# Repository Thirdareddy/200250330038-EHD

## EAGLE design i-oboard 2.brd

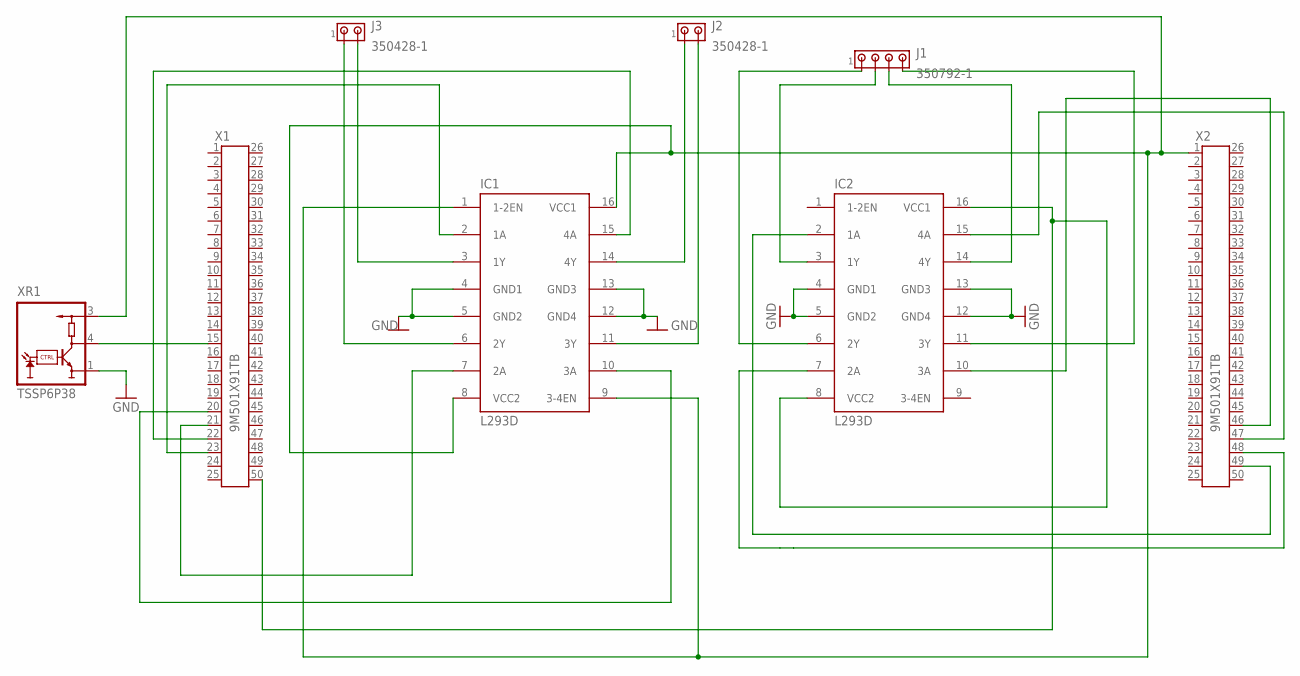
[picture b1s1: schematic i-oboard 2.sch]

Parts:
IC1, IC2: L293D; DIL16
J1: 350792-1
J2, J3: 350428-1
X1, X2: 9M501X91TB; 9M501X91
XR1: TSSP6P38

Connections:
GND: IC1.4 (GND1), IC1.5 (GND2), IC1.12 (GND4), IC1.13 (GND3), IC2.4 (GND1), IC2.5 (GND2), IC2.12 (GND4), IC2.13 (GND3), XR1.1 (GND)
unnamed: IC1.14 (4Y), J2.1
unnamed: IC1.11 (3Y), J2.2
unnamed: IC1.3 (1Y), J3.2
unnamed: IC1.6 (2Y), J3.1
unnamed: IC2.10 (3A), X2.46
unnamed: IC2.7 (2A), X2.48
unnamed: IC2.2 (1A), X2.49
unnamed: IC2.15 (4A), X2.47
unnamed: IC2.8 (VCC2), IC2.16 (VCC1), X1.50
unnamed: X1.15, XR1.4 (OUT)
unnamed: IC2.3 (1Y), J1.2
unnamed: IC2.6 (2Y), J1.1
unnamed: IC2.14 (4Y), J1.3
unnamed: IC2.11 (3Y), J1.4
unnamed: IC1.2 (1A), X1.23
unnamed: IC1.15 (4A), X1.22
unnamed: IC1.7 (2A), X1.21
unnamed: IC1.10 (3A), X1.20
unnamed: IC1.1 (1-2EN), IC1.8 (VCC2), IC1.9 (3-4EN), IC1.16 (VCC1), X2.1, XR1.3 (VS)

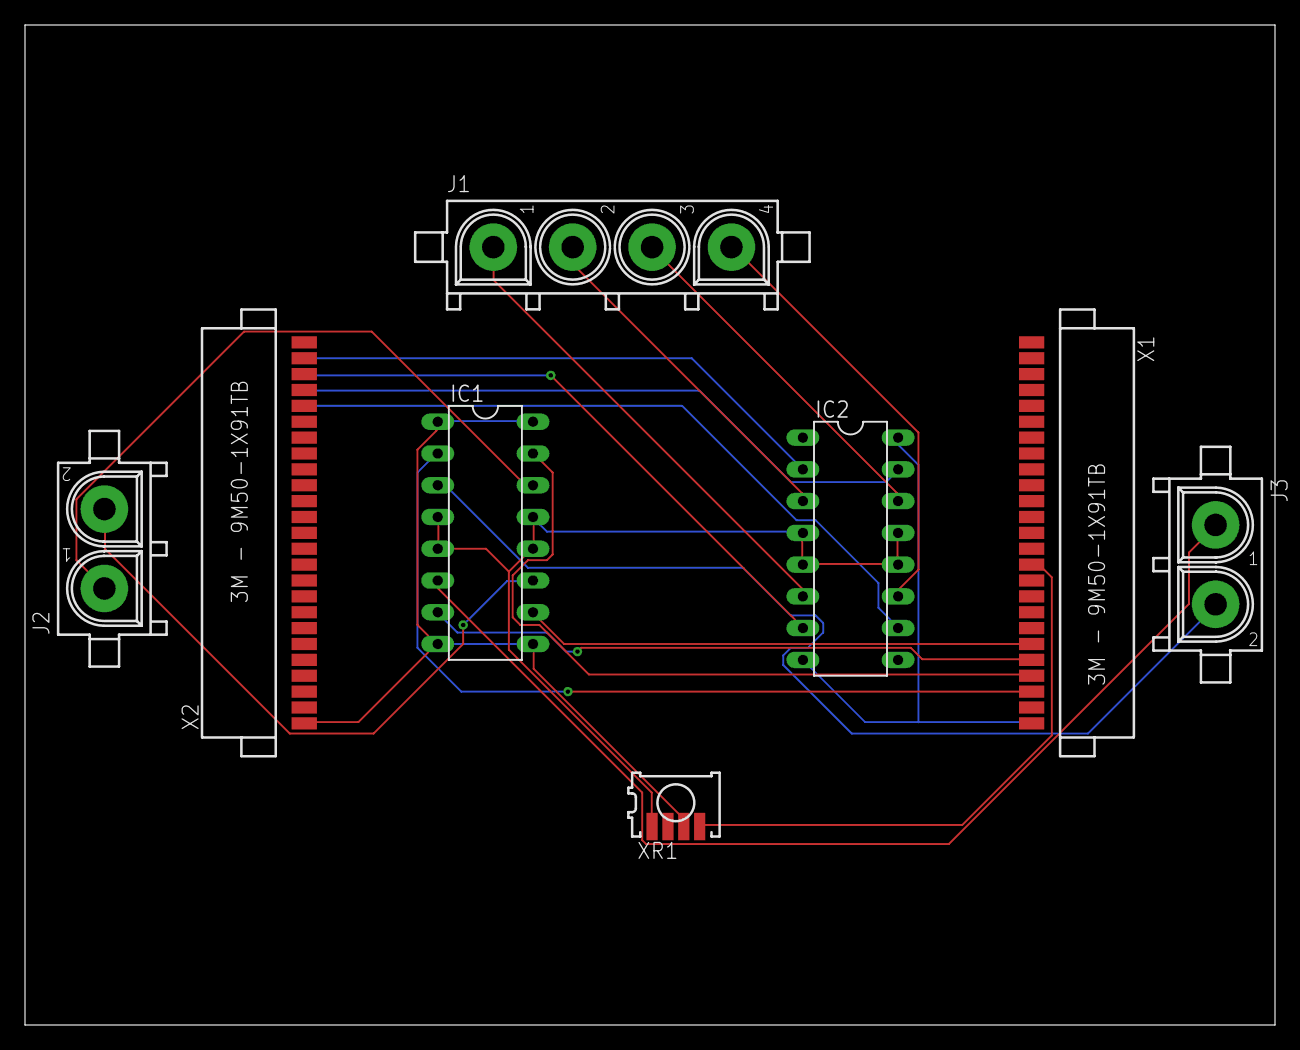
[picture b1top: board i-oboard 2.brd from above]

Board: 2 copper layers, 100.0 x 80.0 mm, 8 parts (0 on the bottom side), 20 nets.

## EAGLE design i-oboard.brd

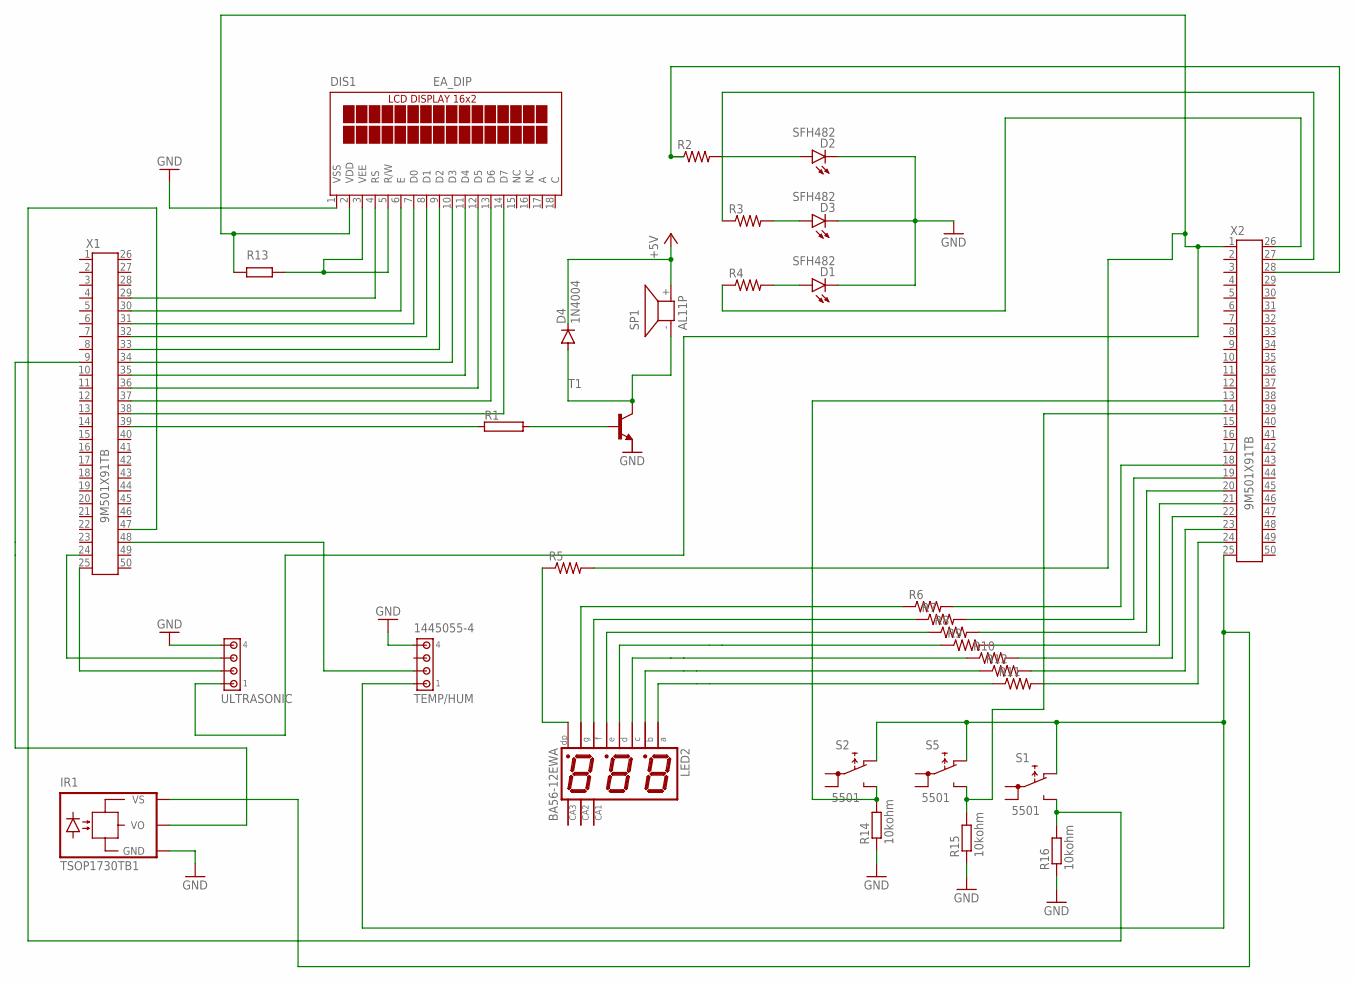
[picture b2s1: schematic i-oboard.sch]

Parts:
D1, D2, D3: SFH482
D4: 1N4004; DO41-10
DIS1: EA_DIP
IR1: TSOP1730TB1; TSOP17_TB1
LED2: BA56-12EWA; BX56-12
R1: RAC01; AC01
R2, R3, R4, R5, R6, R7, R8, R9, R10, R11, R12: R-US_0204/2V; 0204V
R14, R15, R16: 10kohm; 0204V
S1, S2, S5: 5501
SP1: AL11P
T1: -NPN-SOT23-EBC; SOT23-EBC
TEMP/HUM: 1445055-4
ULTRASONIC: 1445055-4
X1, X2: 9M501X91TB; 9M501X91

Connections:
+5V: D4.C, SP1.+ (2)
GND: D1.K (C), D2.K (C), D3.K (C), DIS1.1 (VSS), IR1.GND, R14.1, R15.1, R16.1, TEMP/HUM.4, ULTRASONIC.4
unnamed: LED2.5 (G), R6.1
unnamed: DIS1.7 (D0), X1.31
unnamed: DIS1.8 (D1), X1.32
unnamed: DIS1.9 (D2), X1.33
unnamed: DIS1.10 (D3), X1.34
unnamed: DIS1.11 (D4), X1.35
unnamed: DIS1.12 (D5), X1.36
unnamed: DIS1.13 (D6), X1.37
unnamed: D4.A, SP1.- (1), T1.C
unnamed: DIS1.14 (D7), X1.38
unnamed: DIS1.6 (E), X1.30
unnamed: DIS1.4 (RS), X1.29
unnamed: DIS1.3 (VEE), DIS1.5 (R/W)
unnamed: R1.2, T1.B
unnamed: R1.1, X1.39
unnamed: R4.1, X2.26
unnamed: R3.1, X2.27
unnamed: D2.A, R2.2
unnamed: D3.A, R3.2
unnamed: D1.A, R4.2
unnamed: R11.2, X2.24
unnamed: R12.2, X2.23
unnamed: R10.2, X2.22
unnamed: R9.2, X2.21
unnamed: R8.2, X2.20
unnamed: R7.2, X2.19
unnamed: R6.2, X2.18
unnamed: LED2.3 (DP), R5.1
unnamed: LED2.10 (F), R7.1
unnamed: ULTRASONIC.2, X1.25
unnamed: DIS1.2 (VDD), R5.2, ULTRASONIC.1, X2.1
unnamed: LED2.1 (E), R8.1
unnamed: LED2.2 (D), R9.1
unnamed: LED2.4 (C), R10.1
unnamed: LED2.7 (B), R12.1
unnamed: LED2.11 (A), R11.1
unnamed: ULTRASONIC.3, X1.24
unnamed: R15.2, S5.NO, X2.14
unnamed: R2.1, X2.28
unnamed: TEMP/HUM.2, X1.48
unnamed: IR1.VS, S1.NC, S2.NC, S5.NC, TEMP/HUM.1, X2.25
unnamed: R14.2, S2.NO, X2.13
unnamed: R16.2, S1.NO, X1.47
unnamed: IR1.VO, X1.9

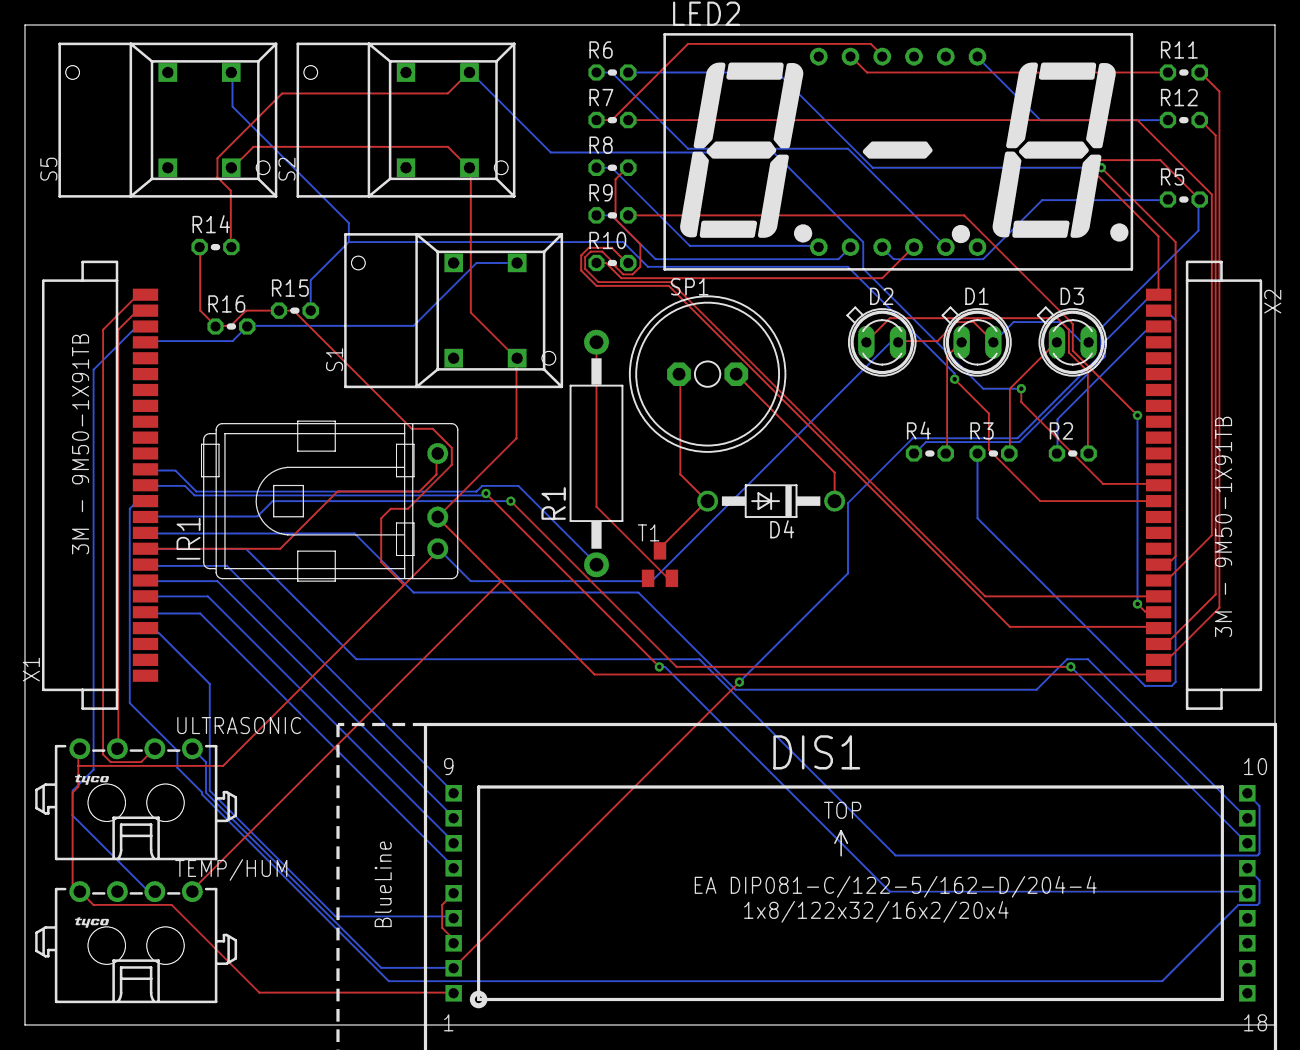
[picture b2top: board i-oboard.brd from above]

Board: 2 copper layers, 100.0 x 80.0 mm, 31 parts (0 on the bottom side), 46 nets.

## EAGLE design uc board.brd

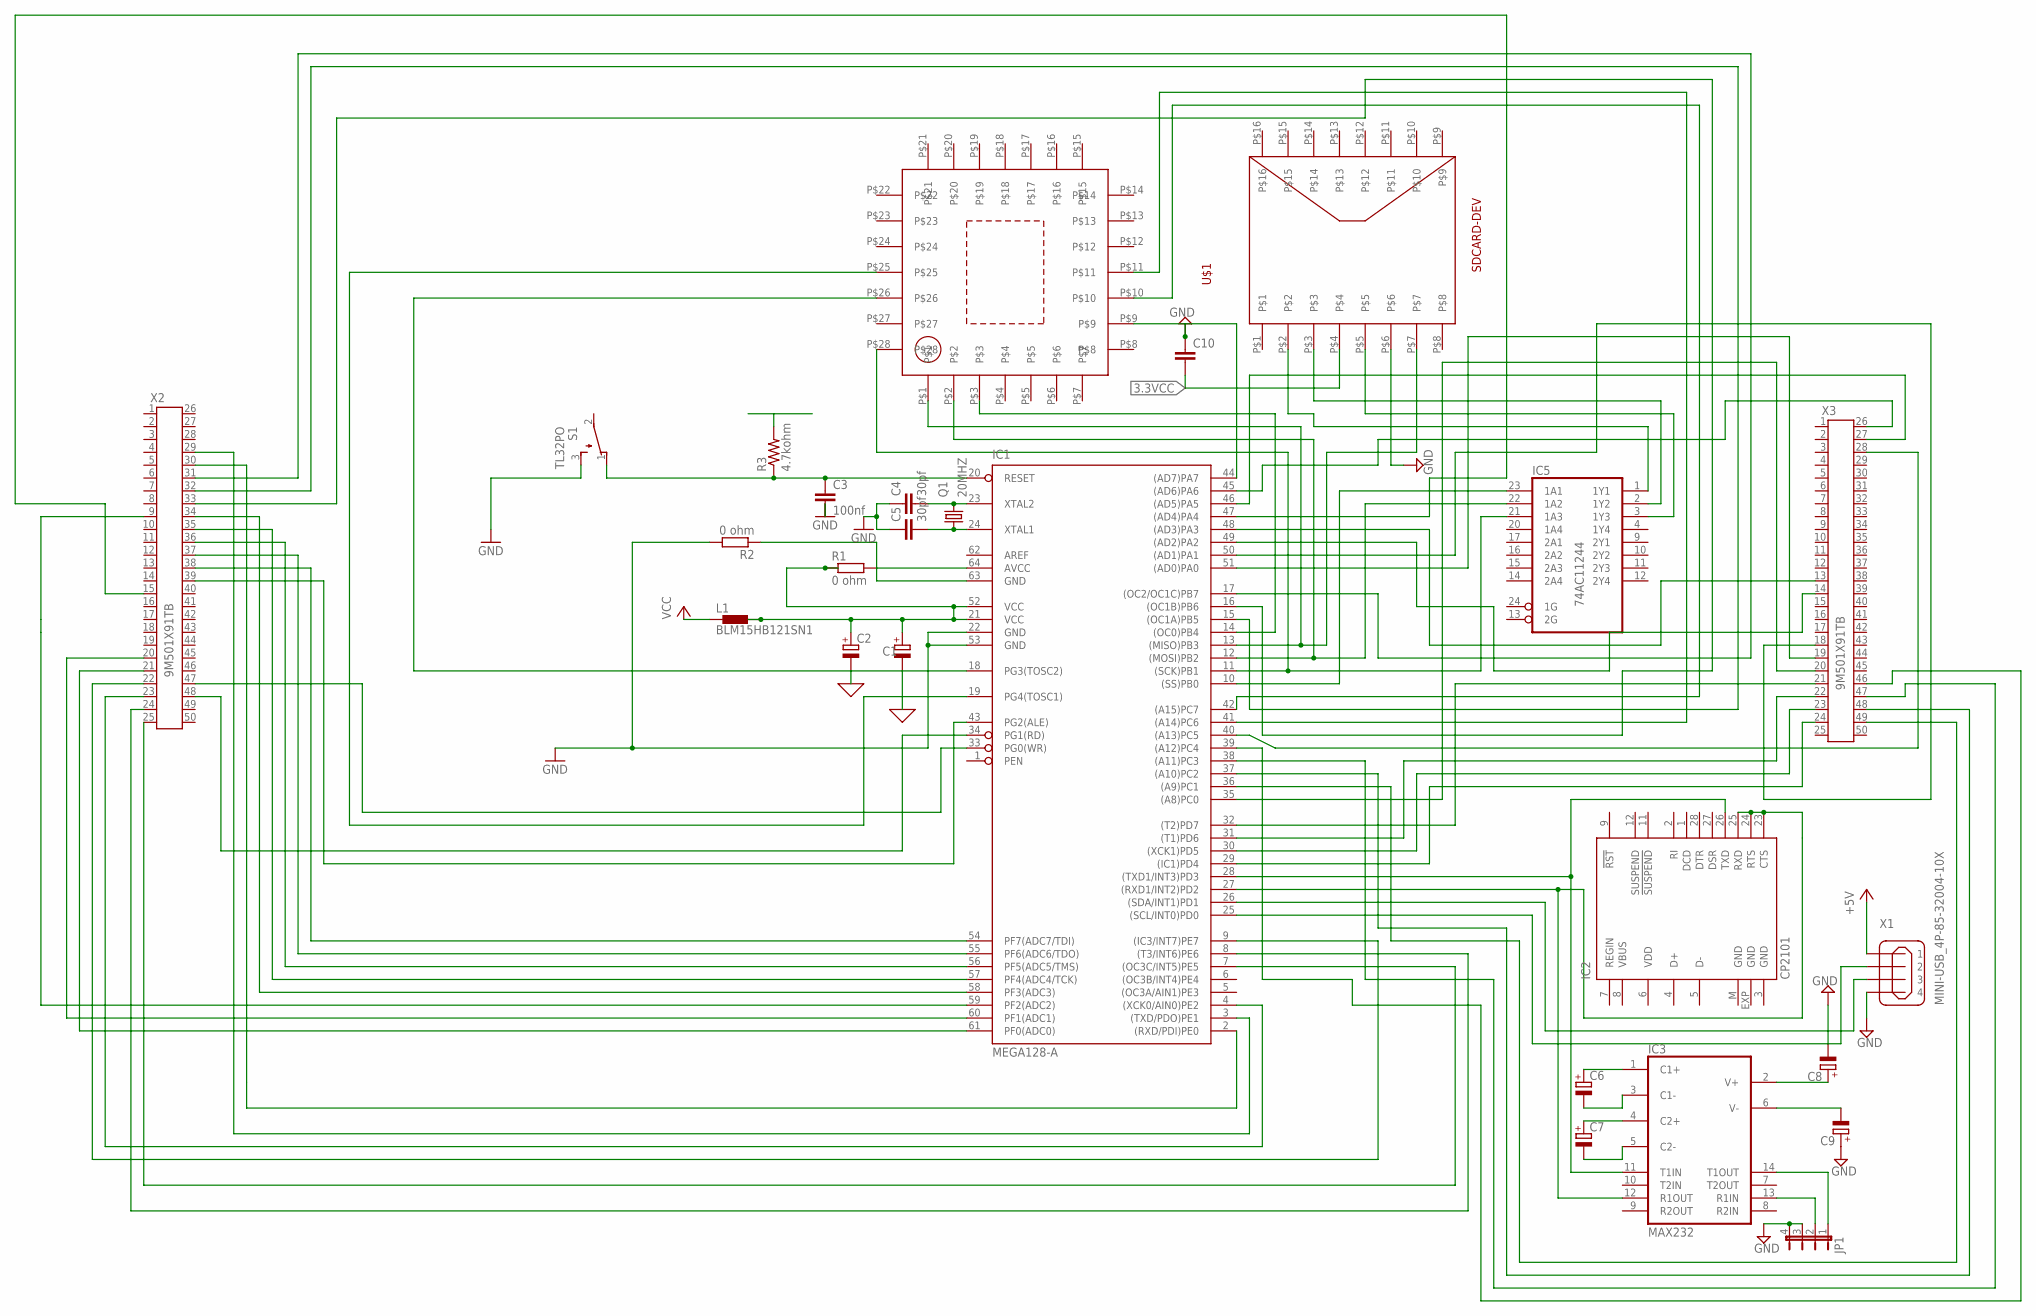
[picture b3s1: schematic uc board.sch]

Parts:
C1, C6, C7, C8, C9: CPOL-EU085CS-1AR; 085CS_1AR
C2: CPOL-EUCT3528; CT3528
C3: 100nf; C2.5-3
C4, C5: 30pf; C2.5-3
C10: C2,5-3; C2.5-3
IC1: MEGA128-A; TQFP64
IC2: CP2101; MLP28
IC3: MAX232; DIL16
IC5: 74AC11244; DIL24-6
JP1: JP4E; JP4
L1: BLM15HB121SN1; 0402
Q1: 20MHZ; 1.6X1.2
R1, R2: 0 ohm; 0204V
R3: 4.7kohm; 0204V
S1: TL32PO; TL3XPO
U$1: SDCARD-DEV; SDCARD-FOOT
U$2: CC2520-ZIGBEE-DEV; CC2520-ZIGBEE-FOOT
X1: MINI-USB_4P-85-32004-10X; 85-32004-10X
X2, X3: 9M501X91TB; 9M501X91

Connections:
0: C1.-, C2.-
3.3VCC: C10.2, U$1.P$4
+5V: X1.1
GND: C3.2, C4.1, C5.1, C8.-, C9.+, C10.1, IC1.22 (GND), IC1.53 (GND), IC2.3 (GND), IC2.EXP (GND), IC2.M (GND), IC3.15 (GND), IC5.5 (GND), IC5.6 (GND), IC5.7 (GND), IC5.8 (GND), JP1.3, JP1.4, R2.2, S1.3 (S), U$1.P$6, X1.4
unnamed: IC1.14 ((OC0)PB4), U$2.P$3
unnamed: IC1.28 ((TXD1/INT3)PD3), IC2.26 (TXD), IC3.11 (T1IN)
unnamed: C3.1, IC1.20 (RESET), R3.1, S1.1 (O)
unnamed: IC1.64 (AVCC), R1.2
unnamed: IC1.27 ((RXD1/INT2)PD2), IC2.23 (CTS), IC2.24 (RTS), IC2.25 (RXD), IC3.12 (R1OUT)
unnamed: IC1.63 (GND), R2.1
unnamed: C4.2, IC1.23 (XTAL2), Q1.3 (2)
unnamed: C5.2, IC1.24 (XTAL1), Q1.1
unnamed: C6.+, IC3.1 (C1+)
unnamed: IC3.14 (T1OUT), JP1.1
unnamed: IC3.13 (R1IN), JP1.2
unnamed: C6.-, IC3.3 (C1-)
unnamed: C7.+, IC3.4 (C2+)
unnamed: C8.+, IC3.2 (V+)
unnamed: C7.-, IC3.5 (C2-)
unnamed: C9.-, IC3.6 (V-)
unnamed: IC1.11 ((SCK)PB1), IC5.21 (1A3), U$2.P$28
unnamed: IC1.12 ((MOSI)PB2), IC5.22 (1A2), U$2.P$2
unnamed: IC1.10 ((SS)PB0), IC5.23 (1A1)
unnamed: IC1.13 ((MISO)PB3), U$1.P$7, U$2.P$1
unnamed: IC5.2 (1Y2), U$1.P$3
unnamed: IC5.3 (1Y3), U$1.P$5
unnamed: IC5.1 (1Y1), U$1.P$2
unnamed: IC1.19 (PG4(TOSC1)), U$2.P$25
unnamed: C1.+, C2.+, IC1.21 (VCC), IC1.52 (VCC), L1.2, R1.1
unnamed: IC1.18 (PG3(TOSC2)), U$2.P$26
unnamed: IC1.44 ((AD7)PA7), U$2.P$9
unnamed: IC1.42 ((A15)PC7), U$2.P$10
unnamed: IC1.41 ((A14)PC6), U$2.P$11
unnamed: IC1.26 ((SDA/INT1)PD1), X1.3
unnamed: IC1.25 ((SCL/INT0)PD0), X1.2
unnamed: IC1.43 (PG2(ALE)), X2.39
unnamed: IC1.54 (PF7(ADC7/TDI)), X2.38
unnamed: IC1.55 (PF6(ADC6/TDO)), X2.37
unnamed: IC1.56 (PF5(ADC5/TMS)), X2.36
unnamed: IC1.57 (PF4(ADC4/TCK)), X2.35
unnamed: IC1.58 (PF3(ADC3)), X2.34
unnamed: IC1.15 ((OC1A)PB5), X2.33
unnamed: IC1.2 ((RXD/PDI)PE0), X2.30
unnamed: IC1.16 ((OC1B)PB6), X2.32
unnamed: IC1.17 ((OC2/OC1C)PB7), X2.31
unnamed: IC1.3 ((TXD/PDO)PE1), X2.29
unnamed: IC1.46 ((AD5)PA5), X3.27
unnamed: IC1.45 ((AD6)PA6), X3.26
unnamed: IC1.40 ((A13)PC5), X3.28
unnamed: IC1.29 ((IC1)PD4), X3.24
unnamed: IC1.31 ((T1)PD6), X3.22
unnamed: IC1.30 ((XCK1)PD5), X3.23
unnamed: IC1.32 ((T2)PD7), X3.21
unnamed: IC1.35 ((A8)PC0), X3.20
unnamed: IC1.7 ((OC3C/INT5)PE5), X2.25
unnamed: IC1.51 ((AD0)PA0), X3.19
unnamed: IC1.50 ((AD1)PA1), X3.18
unnamed: IC1.8 ((T3/INT6)PE6), X2.24
unnamed: IC1.36 ((A9)PC1), X3.49
unnamed: IC1.37 ((A10)PC2), X3.48
unnamed: IC1.38 ((A11)PC3), X3.47
unnamed: IC1.39 ((A12)PC4), X3.46
unnamed: IC1.4 ((XCK0/AIN0)PE2), X2.23
unnamed: IC1.9 ((IC3/INT7)PE7), X2.22
unnamed: IC1.61 (PF0(ADC0)), X2.21
unnamed: IC1.60 (PF1(ADC1)), X2.20
unnamed: IC1.47 ((AD4)PA4), X2.15
unnamed: IC1.34 (PG1(RD)), X2.48
unnamed: IC1.48 ((AD3)PA3), X3.13
unnamed: IC1.49 ((AD2)PA2), X3.14
unnamed: IC1.33 (PG0(WR)), X2.47
unnamed: IC1.59 (PF2(ADC2)), X2.9
VCC: IC3.16 (VCC), IC5.18 (VCC), IC5.19 (VCC), L1.1
VDD: IC2.6 (VDD)

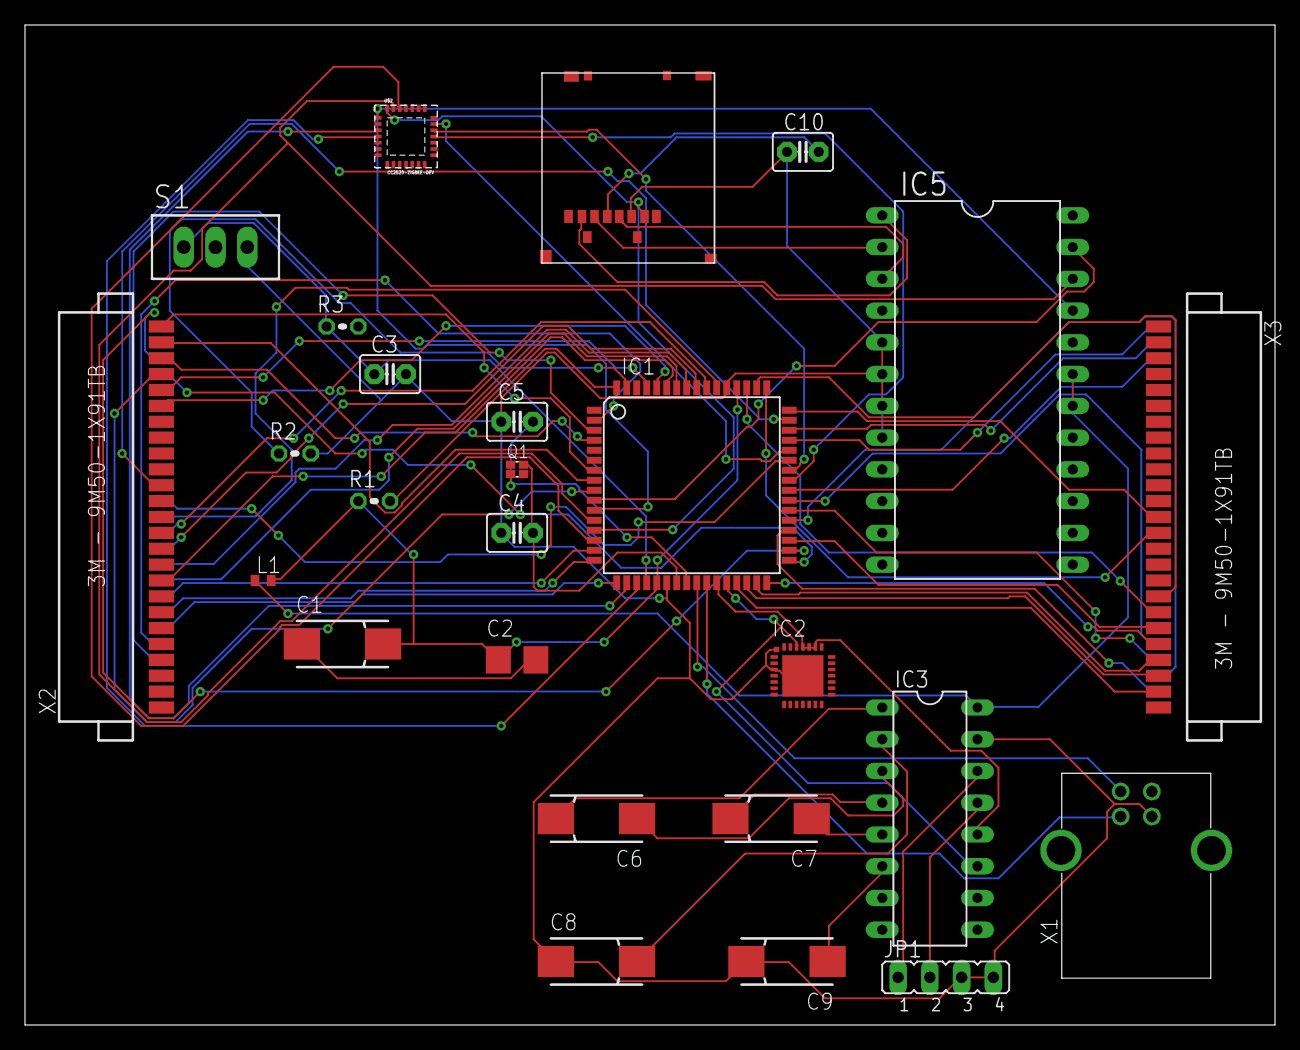
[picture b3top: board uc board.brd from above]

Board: 2 copper layers, 100.0 x 80.0 mm, 26 parts (0 on the bottom side), 72 nets.

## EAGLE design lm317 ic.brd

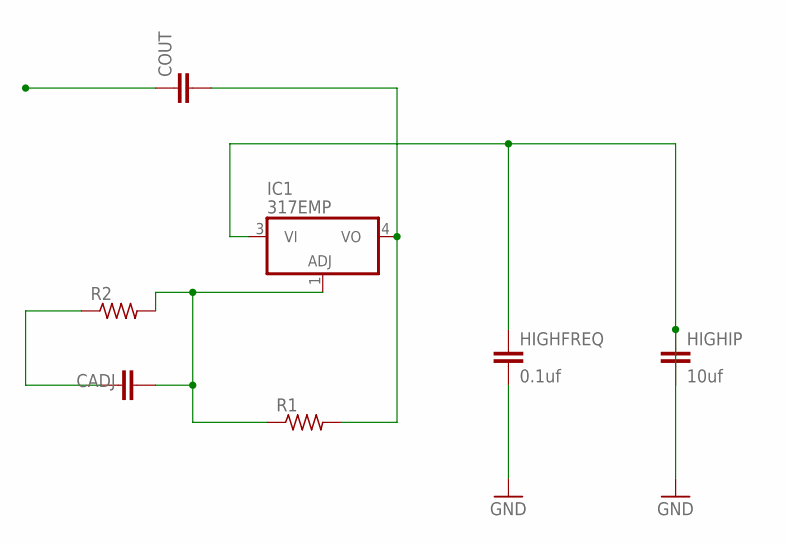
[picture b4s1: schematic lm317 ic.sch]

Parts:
CADJ: C2,5-3; C2.5-3
COUT: C2,5-3; C2.5-3
HIGHFREQ: 0.1uf; C2.5-3
HIGHIP: 10uf; C2.5-3
IC1: 317EMP; SOT223
R1, R2: R-US_0204/2V; 0204V

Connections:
GND: HIGHFREQ.1, HIGHFREQ.2, HIGHIP.1, HIGHIP.2, IC1.3 (VI)
unnamed: CADJ.2, IC1.1 (ADJ), R1.1, R2.2
unnamed: CADJ.1, R2.1
unnamed: COUT.2, IC1.4 (VO), R1.2

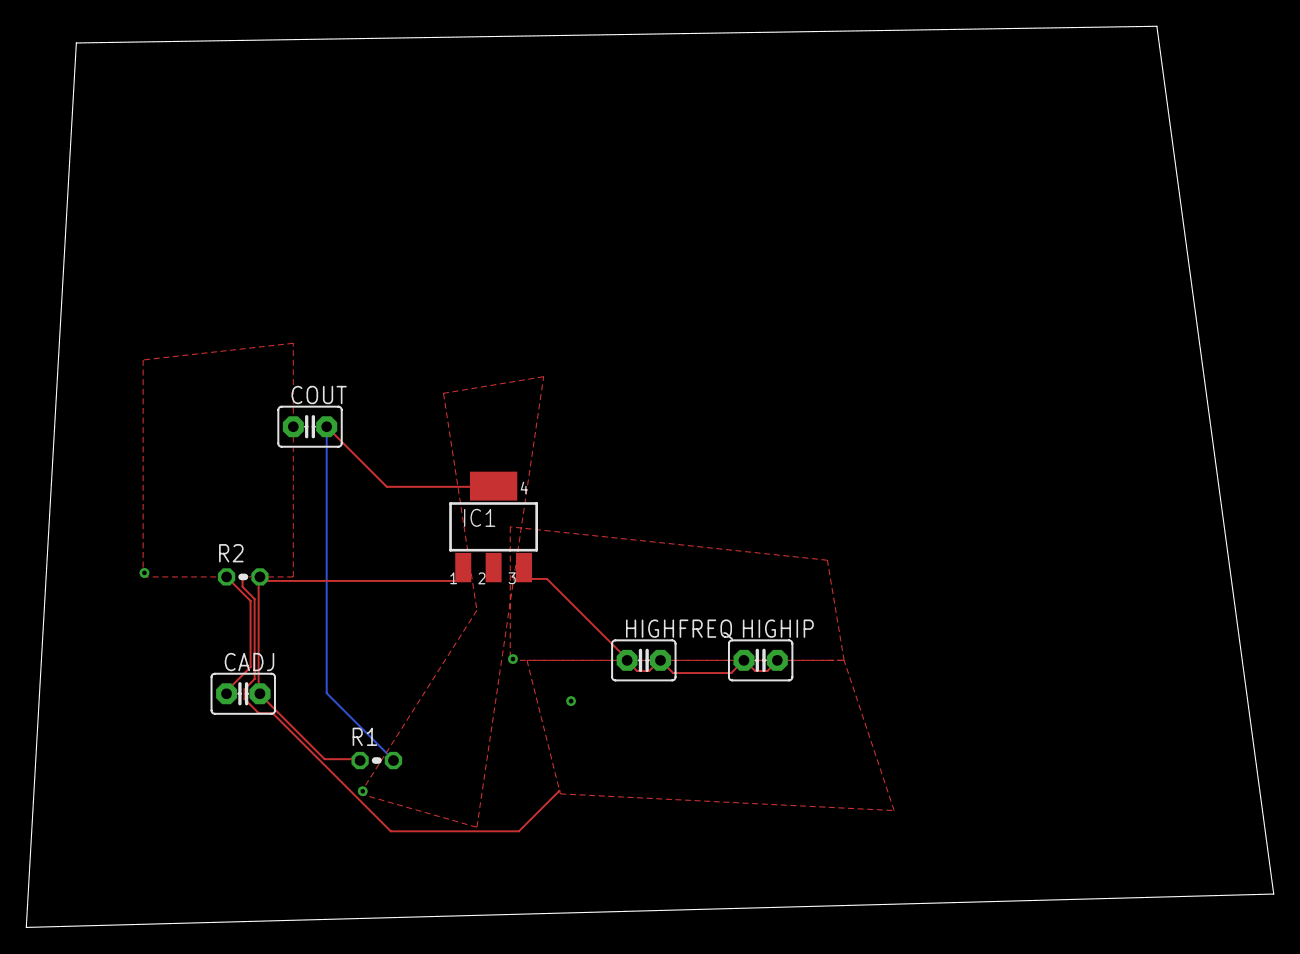
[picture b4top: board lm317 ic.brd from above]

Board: 2 copper layers, 94.9 x 68.6 mm, 7 parts (0 on the bottom side), 4 nets.

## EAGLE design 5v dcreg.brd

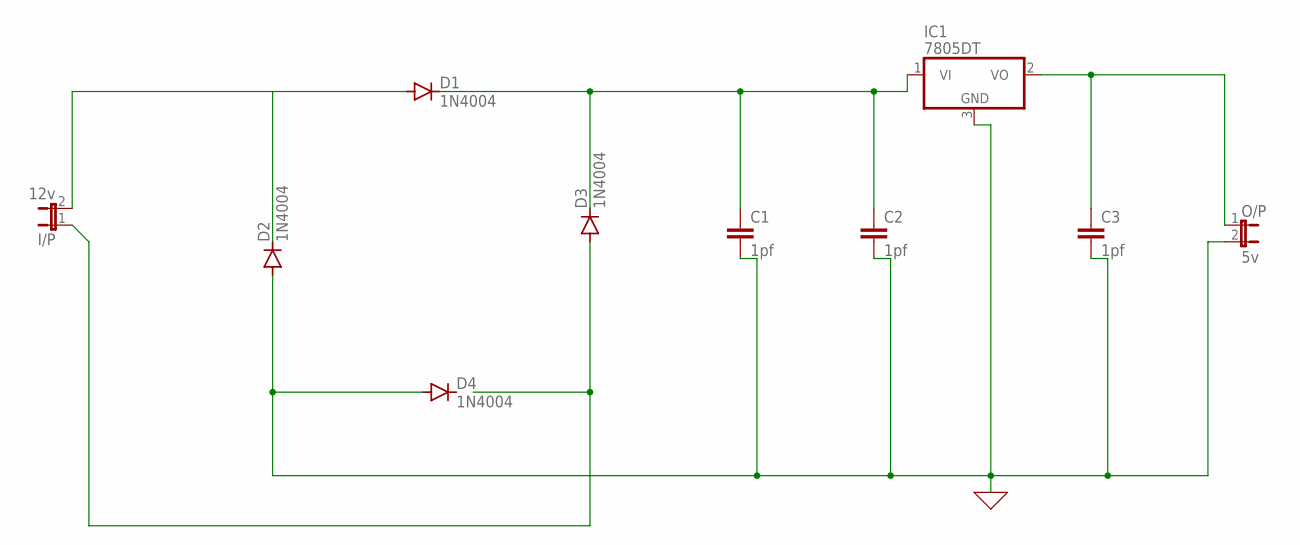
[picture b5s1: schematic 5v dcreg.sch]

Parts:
C1, C2, C3: 1pf; C2.5-3
D1, D2, D3, D4: 1N4004; DO41-10
I/P: 12v; JP1
IC1: 7805DT; TO252
O/P: 5v; JP1

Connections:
0: C1.2, C2.2, C3.2, D2.A, D4.A, IC1.3 (GND), O/P.2
unnamed: D1.A, D2.C, I/P.2
unnamed: C1.1, C2.1, D1.C, D3.C, IC1.1 (VI)
unnamed: D3.A, I/P.1
unnamed: C3.1, IC1.2 (VO), O/P.1

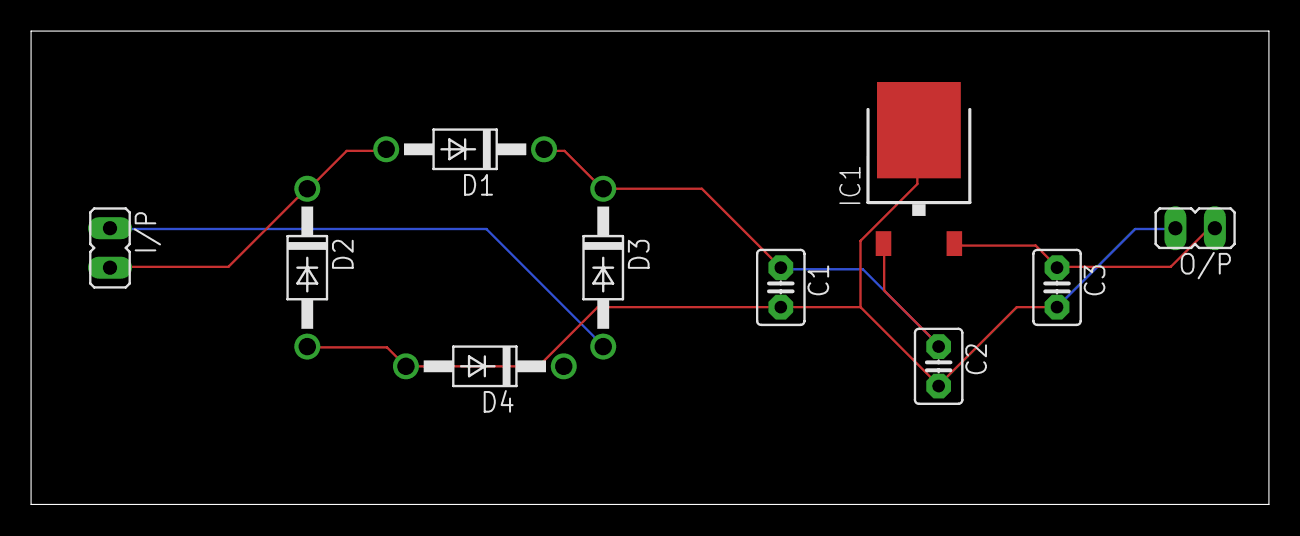
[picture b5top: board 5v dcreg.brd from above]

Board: 2 copper layers, 79.7 x 30.5 mm, 10 parts (0 on the bottom side), 5 nets.

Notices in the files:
parts and their libraries:
crystal-geyer_V1_0: Copyright: Geyer-Electronic
